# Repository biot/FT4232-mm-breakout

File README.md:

The FTDI FT4232H mini module is a breakout board for the FT4232H chip, which
provides four UART ports via a single USB connection. Unfortunately the board
is unpleasant to use, requiring tons of interconnects to be made between the
pins. The pins themselves are unmarked.

This Kicad project is for a breakout board to the mini module, which makes
it easier to use.

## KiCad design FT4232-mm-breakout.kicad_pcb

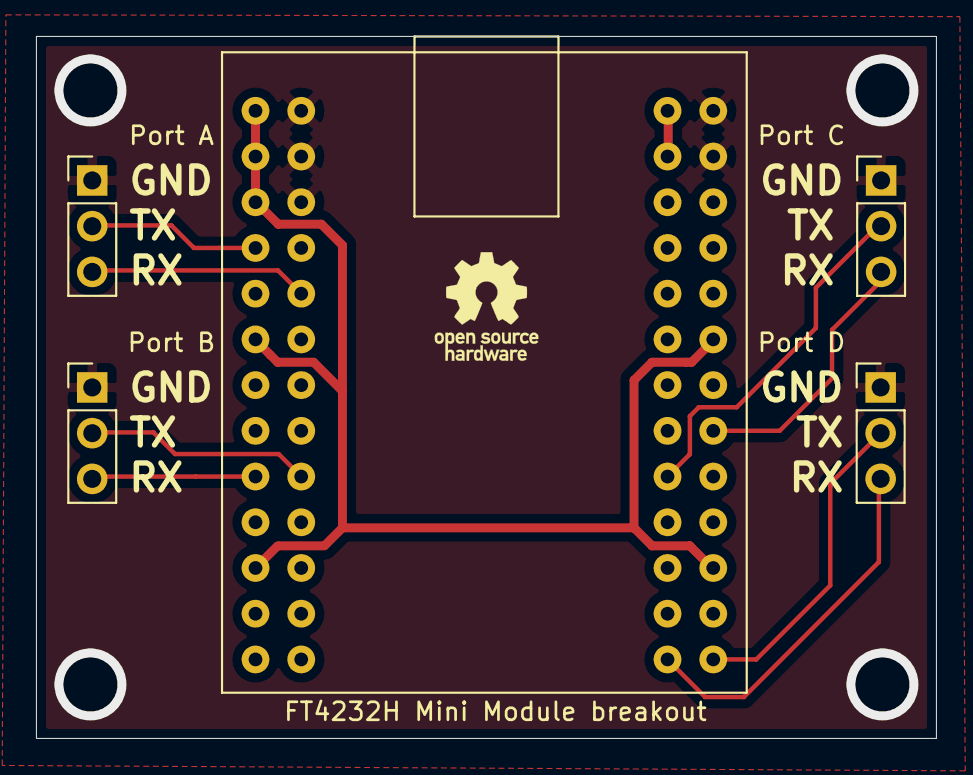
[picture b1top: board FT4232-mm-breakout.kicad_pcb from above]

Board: 2 copper layers, 50.0 x 39.0 mm, 5 parts (0 on the bottom side), 11 nets.

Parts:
M1: FT4232-mini-module
Port A: Conn_01x03_Male; PinHeader_1x03_P2.54mm_Vertical
Port B: Conn_01x03_Male; PinHeader_1x03_P2.54mm_Vertical
Port C: Conn_01x03_Male; PinHeader_1x03_P2.54mm_Vertical
Port D: Conn_01x03_Male; PinHeader_1x03_P2.54mm_Vertical

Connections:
GND: M1.CN2-2, M1.CN2-4, M1.CN2-6, M1.CN3-2, M1.CN3-4, Port A.1, Port B.1, Port C.1, Port D.1
unnamed: M1.CN2-7, Port A.2
unnamed: M1.CN2-10, Port A.3
unnamed: M1.CN2-18, Port B.2
unnamed: M1.CN2-17, Port B.3
unnamed: M1.CN3-17, Port C.2
unnamed: M1.CN3-16, Port C.3
unnamed: M1.CN3-26, Port D.2
unnamed: M1.CN3-25, Port D.3
unnamed: M1.CN2-1, M1.CN2-3, M1.CN2-5, M1.CN2-11, M1.CN2-21, M1.CN3-12, M1.CN3-22
unnamed: M1.CN3-1, M1.CN3-3

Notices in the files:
FT4232-mm-breakout.kicad_pcb:
Copyright (C) 2020 bert@biot.com
